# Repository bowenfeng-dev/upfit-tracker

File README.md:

# UpFit Tracker

Compact and powerful BLE fitness tracker powered by DPS310 high precision pressure sensor.

More project details:
https://www.hackster.io/bowenfeng/upfit-tracker-1a527d

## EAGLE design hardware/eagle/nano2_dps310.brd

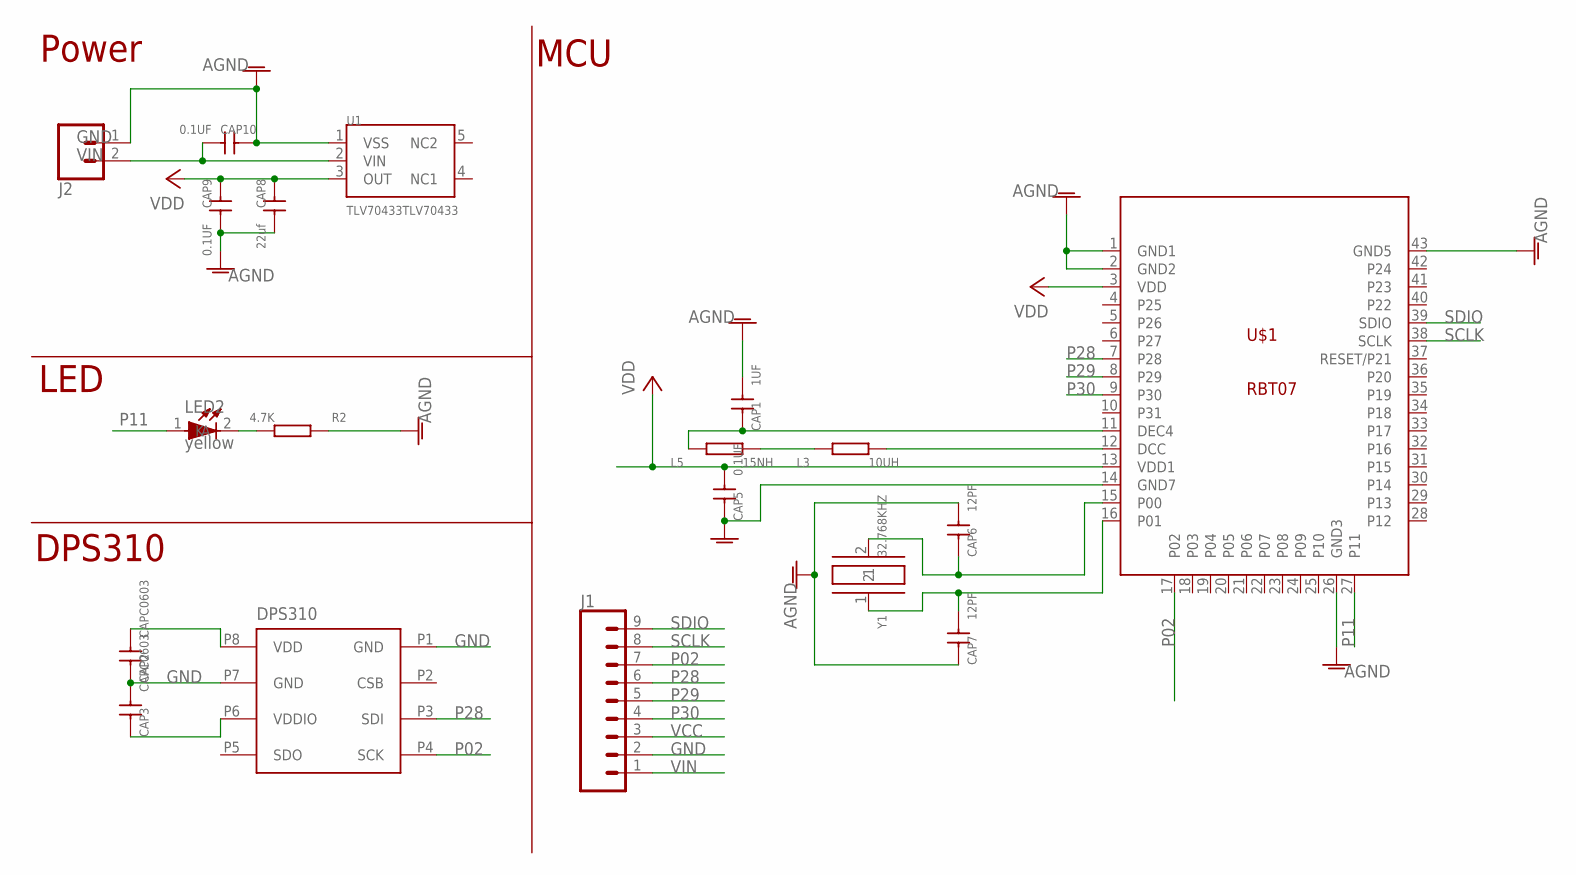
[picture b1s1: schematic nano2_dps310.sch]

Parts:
CAP1: 1UF; C-0402
CAP2, CAP3: CAPC0603; C0603
CAP5, CAP9, CAP10: 0.1UF; C-0402
CAP6, CAP7: 12PF; C-0402
CAP8: 22uf; C0805
J1: CONN_09LOCK; 1X09_LOCK
J2: CONN_02JST-PTH-2; JST-2-PTH
L3: 10UH; R0603
L5: 15NH; R0402
LED2: yellow; LED0603
R2: 4.7K; R0402
U1: TLV70433TLV70433; SOT-23-5
U2: DPS310; LGA-8
U$1: RBT07
Y1: 32.768KHZ; CRY_3215

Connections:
GND: CAP1.1, CAP2.2, CAP3.1, CAP5.2, CAP6.1, CAP7.2, CAP8.1, CAP9.1, CAP10.2, J1.2, J2.1, R2.1, U1.1 (VSS), U2.P1 (GND), U2.P7 (GND), U$1.1 (GND1), U$1.2 (GND2), U$1.14 (GND7), U$1.26 (GND3), U$1.43 (GND5)
unnamed: L3.2, U$1.12 (DCC)
unnamed: L3.1, L5.2
unnamed: CAP1.2, L5.1, U$1.11 (DEC4)
unnamed: CAP6.2, U$1.15 (P00), Y1.2
unnamed: LED2.2 (K), R2.2
unnamed: CAP7.1, U$1.16 (P01), Y1.1
P02: J1.7, U2.P4 (SCK), U$1.17 (P02)
P11: LED2.1 (A), U$1.27 (P11)
P28: J1.6, U2.P3 (SDI), U$1.7 (P28)
P29: J1.5, U$1.8 (P29)
P30: J1.4, U$1.9 (P30)
SCLK: J1.8, U$1.38 (SCLK)
SDIO: J1.9, U$1.39 (SDIO)
VCC: CAP2.1, CAP3.2, CAP5.1, CAP8.2, CAP9.2, J1.3, U1.3 (OUT), U2.P6 (VDDIO), U2.P8 (VDD), U$1.3 (VDD), U$1.13 (VDD1)
VIN: CAP10.1, J1.1, J2.2, U1.2 (VIN)

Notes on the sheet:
LED
DPS310
Power
MCU

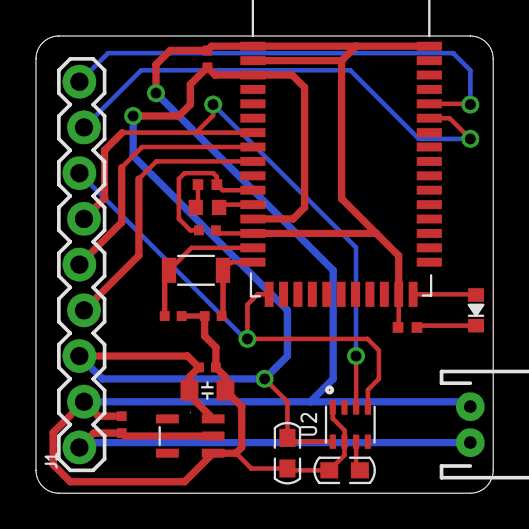
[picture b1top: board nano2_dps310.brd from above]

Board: 2 copper layers, 25.4 x 25.4 mm, 19 parts (0 on the bottom side), 16 nets.

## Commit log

2017-09-27 Add readme
2017-09-27 Add hardware Eagle files
2017-09-30 Android app UI polishing

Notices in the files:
parts and their libraries:
SparkFun-Connectors: Licensing: Creative Commons ShareAlike 4.0 International - https://creativecommons.org/licenses/by-sa/4.0
